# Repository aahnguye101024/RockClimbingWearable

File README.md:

# RockClimbingWearable

The rock climbing wearable should serve as a portable device worn around one's waist when they rock climb. Operating with a lipo battery, this device uses an active GPS device, an OLED screen, and a TEENSY-LC to track your vertical distance climbed for your own training purposes.

## Board Pictures

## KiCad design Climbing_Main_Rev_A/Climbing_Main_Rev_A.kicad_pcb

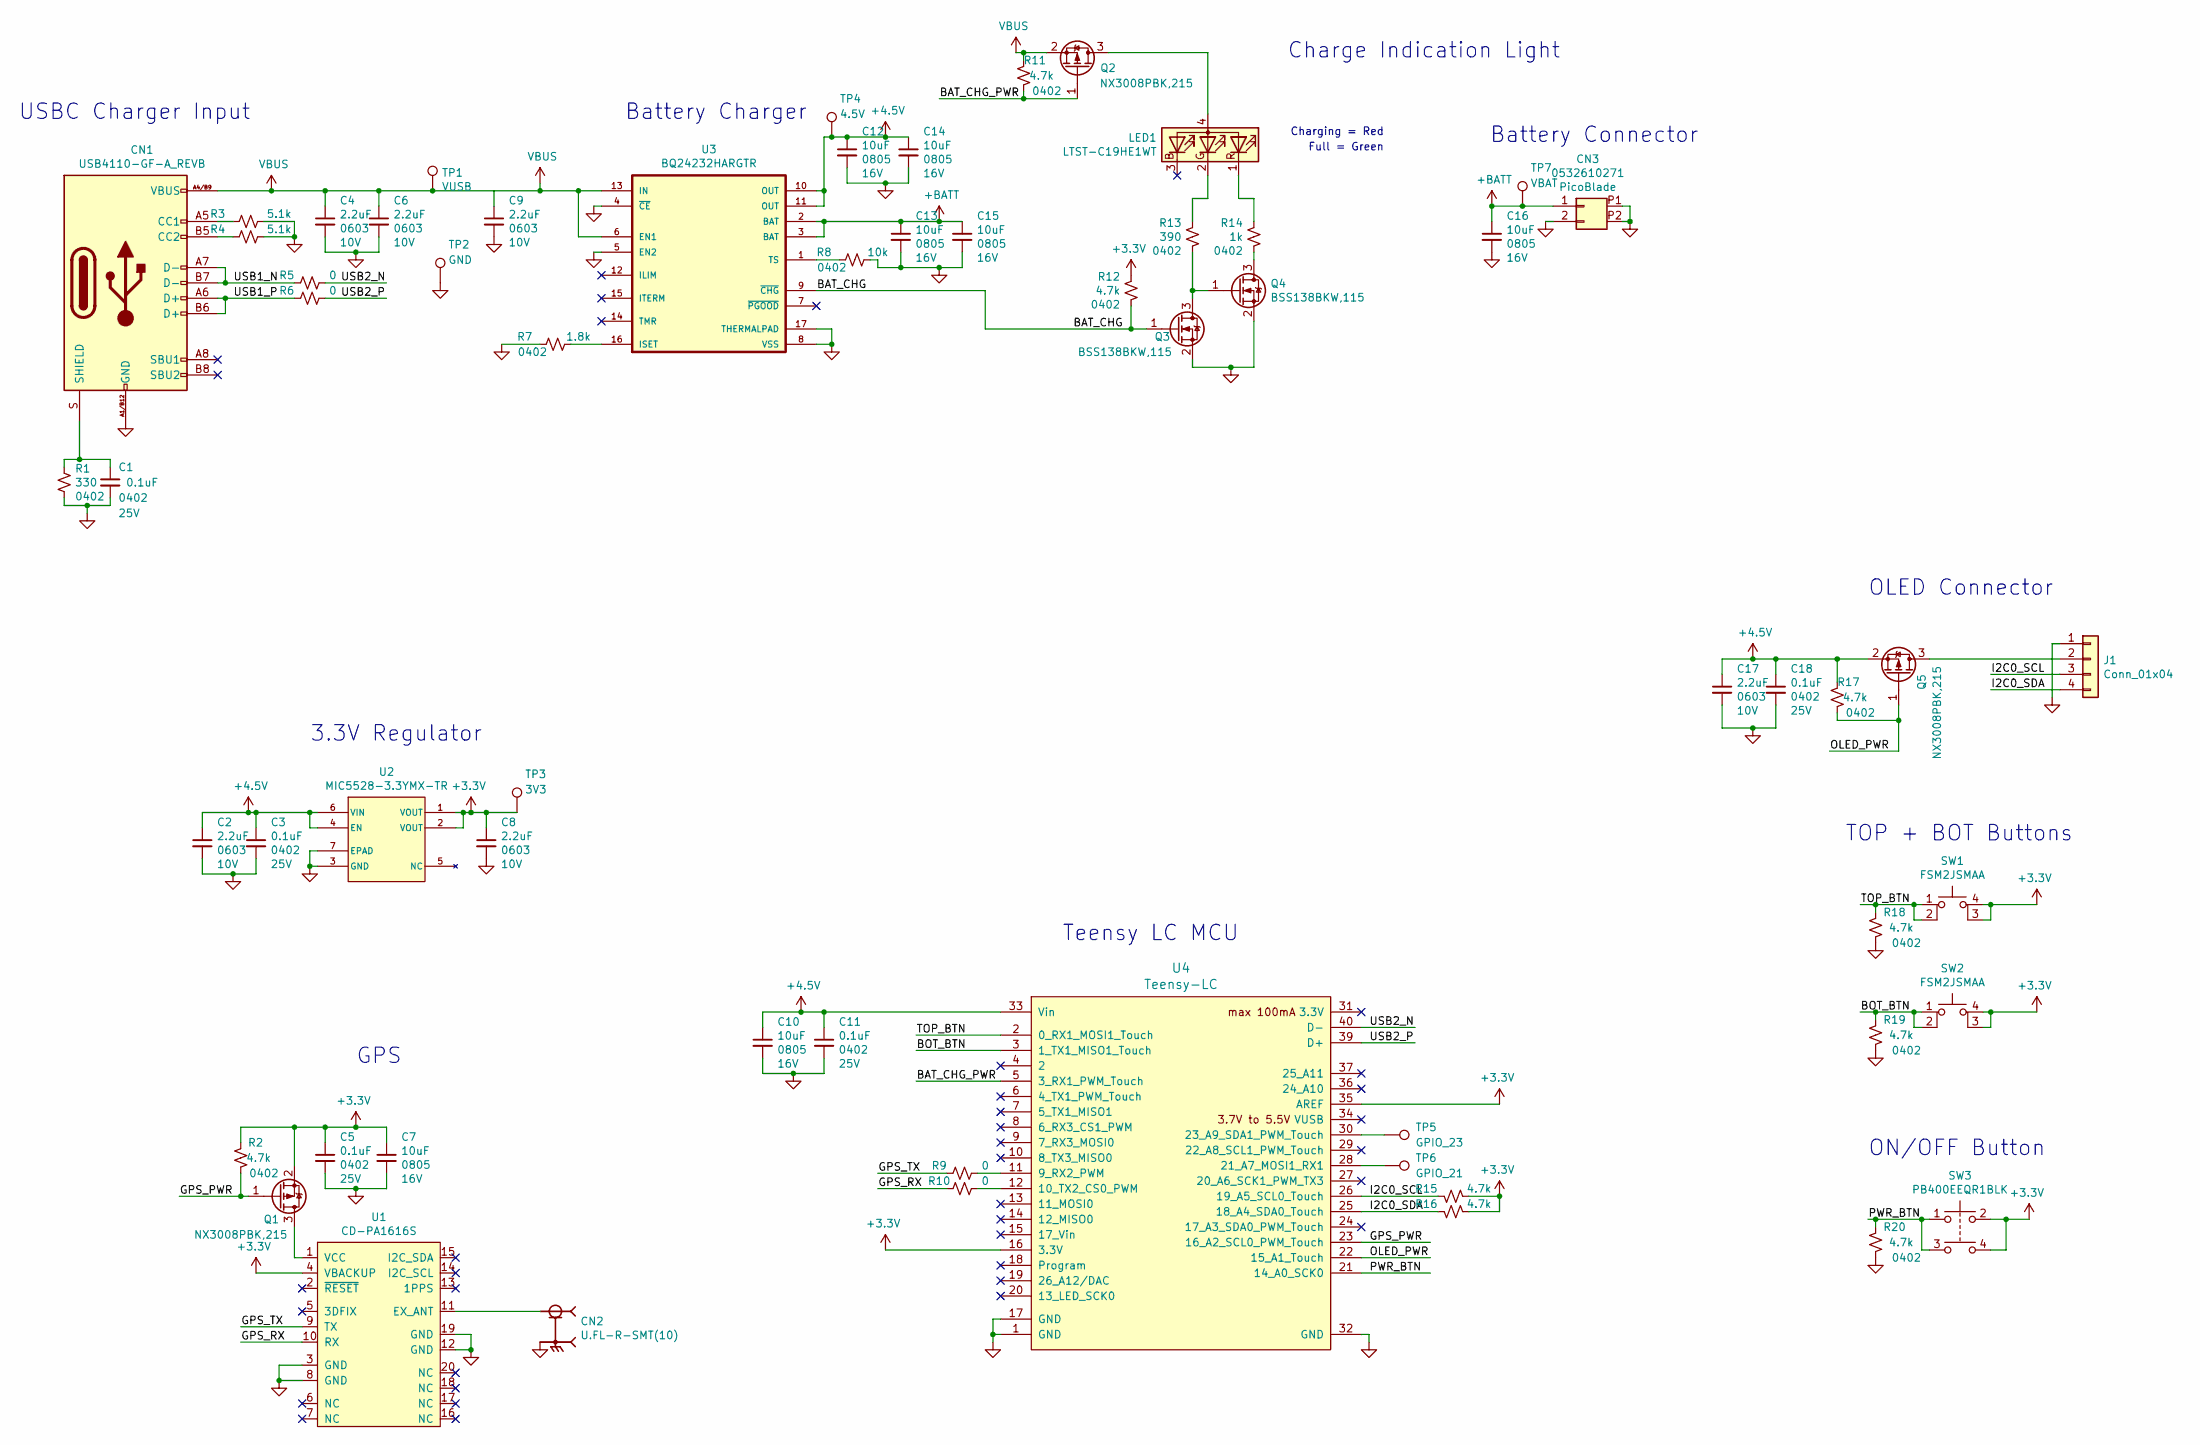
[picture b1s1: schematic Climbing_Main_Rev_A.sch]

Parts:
C1, C3, C5, C11, C18: 0.1uF; C_0402_1005Metric; Voltage 25V; Part Number 1276-1043-1-ND
C2, C4, C6, C8, C9, C17: 2.2uF; C_0603_1608Metric; Voltage 10V; Part Number 1276-1085-1-ND
C7, C10, C12, C13, C14, C15, C16: 10uF; C_0805_2012Metric; Voltage 16V; Part Number 1276-2893-1-ND
CN1: USB4110-GF-A_REVB; GCT_USB4110-GF-A_REVB; Part Number 2073-USB4110-GF-A-1-ND
CN2: U.FL-R-SMT(10); HRS_U.FL-R-SMT(10); Part Number H9161CT-ND
CN3: 0532610271; MOLEX_53261-0271; Part Number WM7620CT-ND
J1: Conn_01x04; PinHeader_1x04_P2.54mm_Vertical
LED1: LTST-C19HE1WT; LED_LTST-C19HE1WT; Part Number 160-2162-1-ND
Q1, Q2, Q5: NX3008PBK,215; SOT-23; Part Number 1727-1281-1-ND
Q3, Q4: BSS138BKW,115; SOT-323_SC-70; Part Number 1727-1262-1-ND
R1: 330; R_0402_1005Metric; Part Number 311-330LRCT-ND
R2, R11, R12, R15, R16, R17, R18, R19, R20: 4.7k; R_0402_1005Metric; Part Number RMCF0402FT4K70CT-ND
R3, R4: 5.1k; R_0402_1005Metric; Part Number 311-5.10KLRCT-ND
R5, R6, R9, R10: 0; R_0402_1005Metric; Part Number RMCF0402ZT0R00CT-ND
R7: 1.8k; R_0402_1005Metric; Part Number RMCF0402FT1K80CT-ND
R8: 10k; R_0402_1005Metric; Part Number RMCF0402FT10K0CT-ND
R13: 390; R_0402_1005Metric; Part Number RMCF0402FT390RCT-ND
R14: 1k; R_0402_1005Metric; Part Number RMCF0402FT1K00CT-ND
SW1, SW2: FSM2JSMAA; SW_2-1437565-8; Part Number 450-3355-ND
SW3: PB400EEQR1BLK; Part Number EG5547-ND
TP1: VUSB; CurrentTestPoint
TP2: GND; CurrentTestPoint
TP3: 3V3; CurrentTestPoint
TP4: 4.5V; CurrentTestPoint
TP5: GPIO_23; CurrentTestPoint
TP6: GPIO_21; CurrentTestPoint
TP7: VBAT; CurrentTestPoint
U1: CD-PA1616S; PA1616S; Part Number 1528-5186-ND
U2: MIC5528-3.3YMX-TR; Part Number 576-4452-1-ND
U3: BQ24232HARGTR; QFN50P300X300X100-17N; Part Number 296-49554-1-ND
U4: Teensy-LC; Teensy_LC; Part Number 1568-1233-ND

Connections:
+3V3: C5.1, C7.1, C8.1, Q1.2 (S), R2.1, R12.1, R15.2, R16.2, SW1.3 (K), SW1.4 (A), SW2.3 (K), SW2.4 (A), SW3.2, SW3.4, TP3.1, U1.4 (VBACKUP), U2.1 (VOUT), U2.2 (VOUT), U4.16 (3.3V), U4.35 (AREF)
+4V2: C2.1, C3.1, C10.1, C11.1, C12.1, C14.1, C17.1, C18.1, Q5.2 (S), R17.1, TP4.1, U2.4 (EN), U2.6 (VIN), U3.10 (OUT), U3.11 (OUT), U4.33 (Vin)
+BATT: C13.1, C15.1, C16.1, CN3.1, TP7.1, U3.2 (BAT), U3.3 (BAT)
/BAT_CHG: Q3.1 (G), R12.2, U3.9 (~CHG)
/BAT_CHG_PWR: Q2.1 (G), R11.2, U4.5 (3_RX1_PWM_Touch)
/BOT_BTN: R19.1, SW2.1, SW2.2, U4.3 (1_TX1_MISO1_Touch)
/GPS_PWR: Q1.1 (G), R2.2, U4.23 (16_A2_SCL0_PWM_Touch)
/GPS_RX: R10.2, U1.10 (RX)
/GPS_TX: R9.2, U1.9 (TX)
/I2C0_SCL: J1.3, R15.1, U4.26 (19_A5_SCL0_Touch)
/I2C0_SDA: J1.4, R16.1, U4.25 (18_A4_SDA0_Touch)
/OLED_PWR: Q5.1 (G), R17.2, U4.22 (15_A1_Touch)
/PWR_BTN: R20.1, SW3.1, SW3.3, U4.21 (14_A0_SCK0)
/TOP_BTN: R18.1, SW1.1, SW1.2, U4.2 (0_RX1_MOSI1_Touch)
/USB1_N: CN1.A7 (D-), CN1.B7 (D-), R5.2
/USB1_P: CN1.A6 (D+), CN1.B6 (D+), R6.2
/USB2_N: R5.1, U4.40 (D-)
/USB2_P: R6.1, U4.39 (D+)
GND: C1.2, C2.2, C3.2, C4.2, C5.2, C6.2, C7.2, C8.2, C9.2, C10.2, C11.2, C12.2, C13.2, C14.2, C15.2, C16.2, C17.2, C18.2, CN1.A1/B12 (GND), CN1.B1/A12 (GND), CN2.2, CN2.3, CN3.2, CN3.P1 (TAB), CN3.P2 (TAB), J1.1, Q3.2 (S), Q4.2 (S), R1.2, R3.1, R4.1, R7.2, R8.1, R18.2, R19.2, R20.2, TP2.1, U1.3 (GND), U1.8 (GND), U1.12 (GND), U1.19 (GND), U2.3 (GND), U2.7 (EPAD), U3.4 (~CE), U3.5 (EN2), U3.8 (VSS), U3.17 (THERMALPAD), U4.1 (GND), U4.17 (GND), U4.32 (GND)
unnamed: C1.1, CN1.S (SHIELD), R1.1
unnamed: CN1.A5 (CC1), R3.2
unnamed: CN1.B5 (CC2), R4.2
unnamed: CN2.1, U1.11 (EX_ANT)
unnamed: J1.2, Q5.3 (D)
unnamed: LED1.1 (RK), R14.1
unnamed: LED1.2 (GK), R13.1
unnamed: LED1.4 (A), Q2.3 (D)
unnamed: Q1.3 (D), U1.1 (VCC)
unnamed: Q3.3 (D), Q4.1 (G), R13.2
unnamed: Q4.3 (D), R14.2
unnamed: R7.1, U3.16 (ISET)
unnamed: R8.2, U3.1 (TS)
unnamed: R9.1, U4.11 (9_RX2_PWM)
unnamed: R10.1, U4.12 (10_TX2_CS0_PWM)
unnamed: TP5.1, U4.30 (23_A9_SDA1_PWM_Touch)
unnamed: TP6.1, U4.28 (21_A7_MOSI1_RX1)
VBUS: C4.1, C6.1, C9.1, CN1.A4/B9 (VBUS), CN1.B4/A9 (VBUS), Q2.2 (S), R11.1, TP1.1, U3.6 (EN1), U3.13 (IN)

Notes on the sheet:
Battery Charger
USBC Charger Input
Charge Indication Light
Full = Green
Charging = Red
3.3V Regulator
Battery Connector
GPS
Teensy LC MCU
OLED Connector
TOP + BOT Buttons
ON/OFF Button

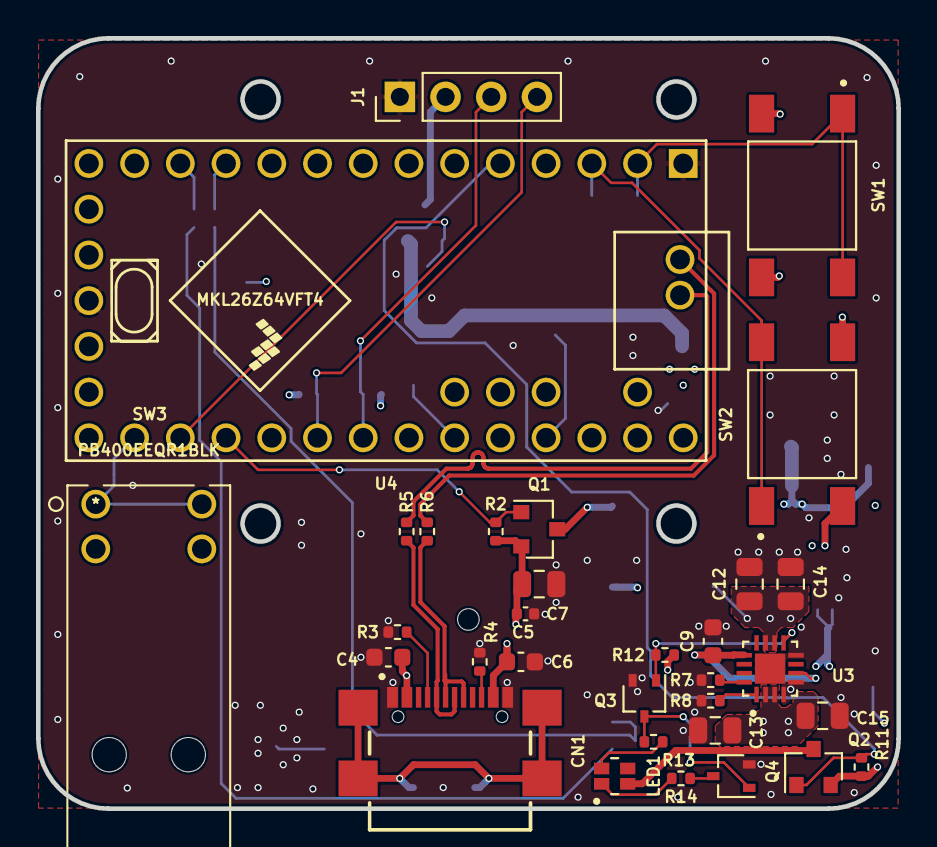
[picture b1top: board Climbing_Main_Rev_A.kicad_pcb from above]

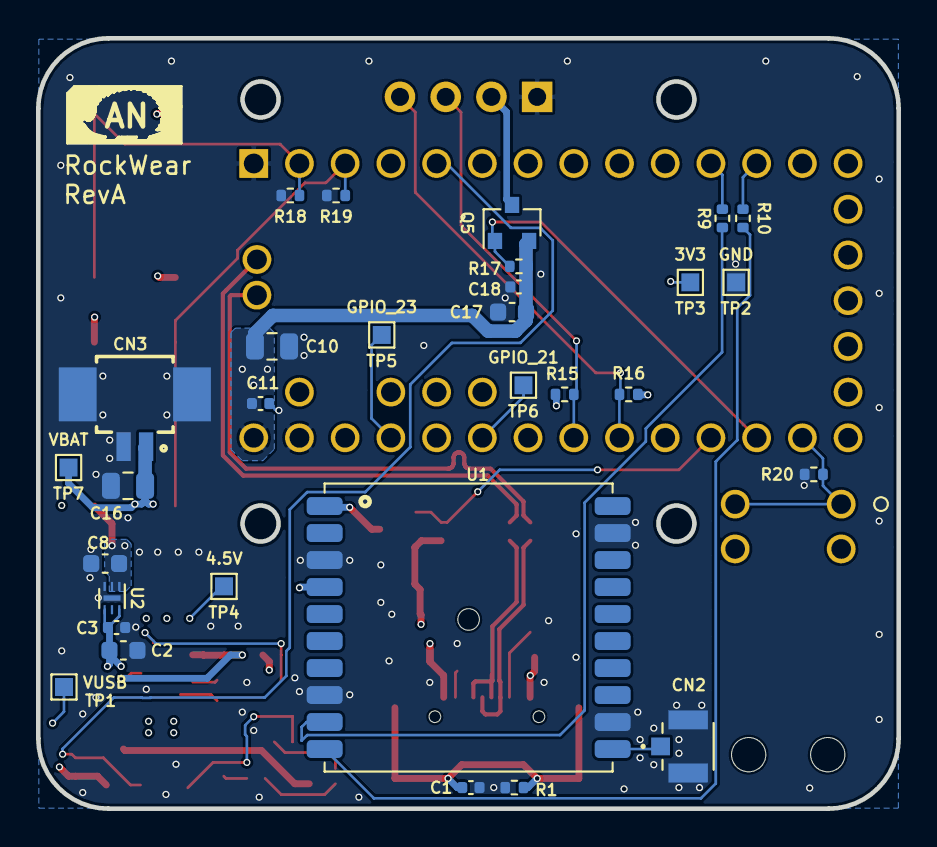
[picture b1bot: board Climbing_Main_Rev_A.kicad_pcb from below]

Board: 4 copper layers, 47.8 x 42.8 mm, 62 parts (30 on the bottom side), 37 nets.

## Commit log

2024-01-31 added everything
2024-01-31 picture support for readme

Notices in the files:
parts and their libraries:
Copyright 2021 Accelerated Designs. All rights reserved.
